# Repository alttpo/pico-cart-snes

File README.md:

# pico-cart-snes
Raspberry Pi Pico SNES flash cart (no SD card, WIP)

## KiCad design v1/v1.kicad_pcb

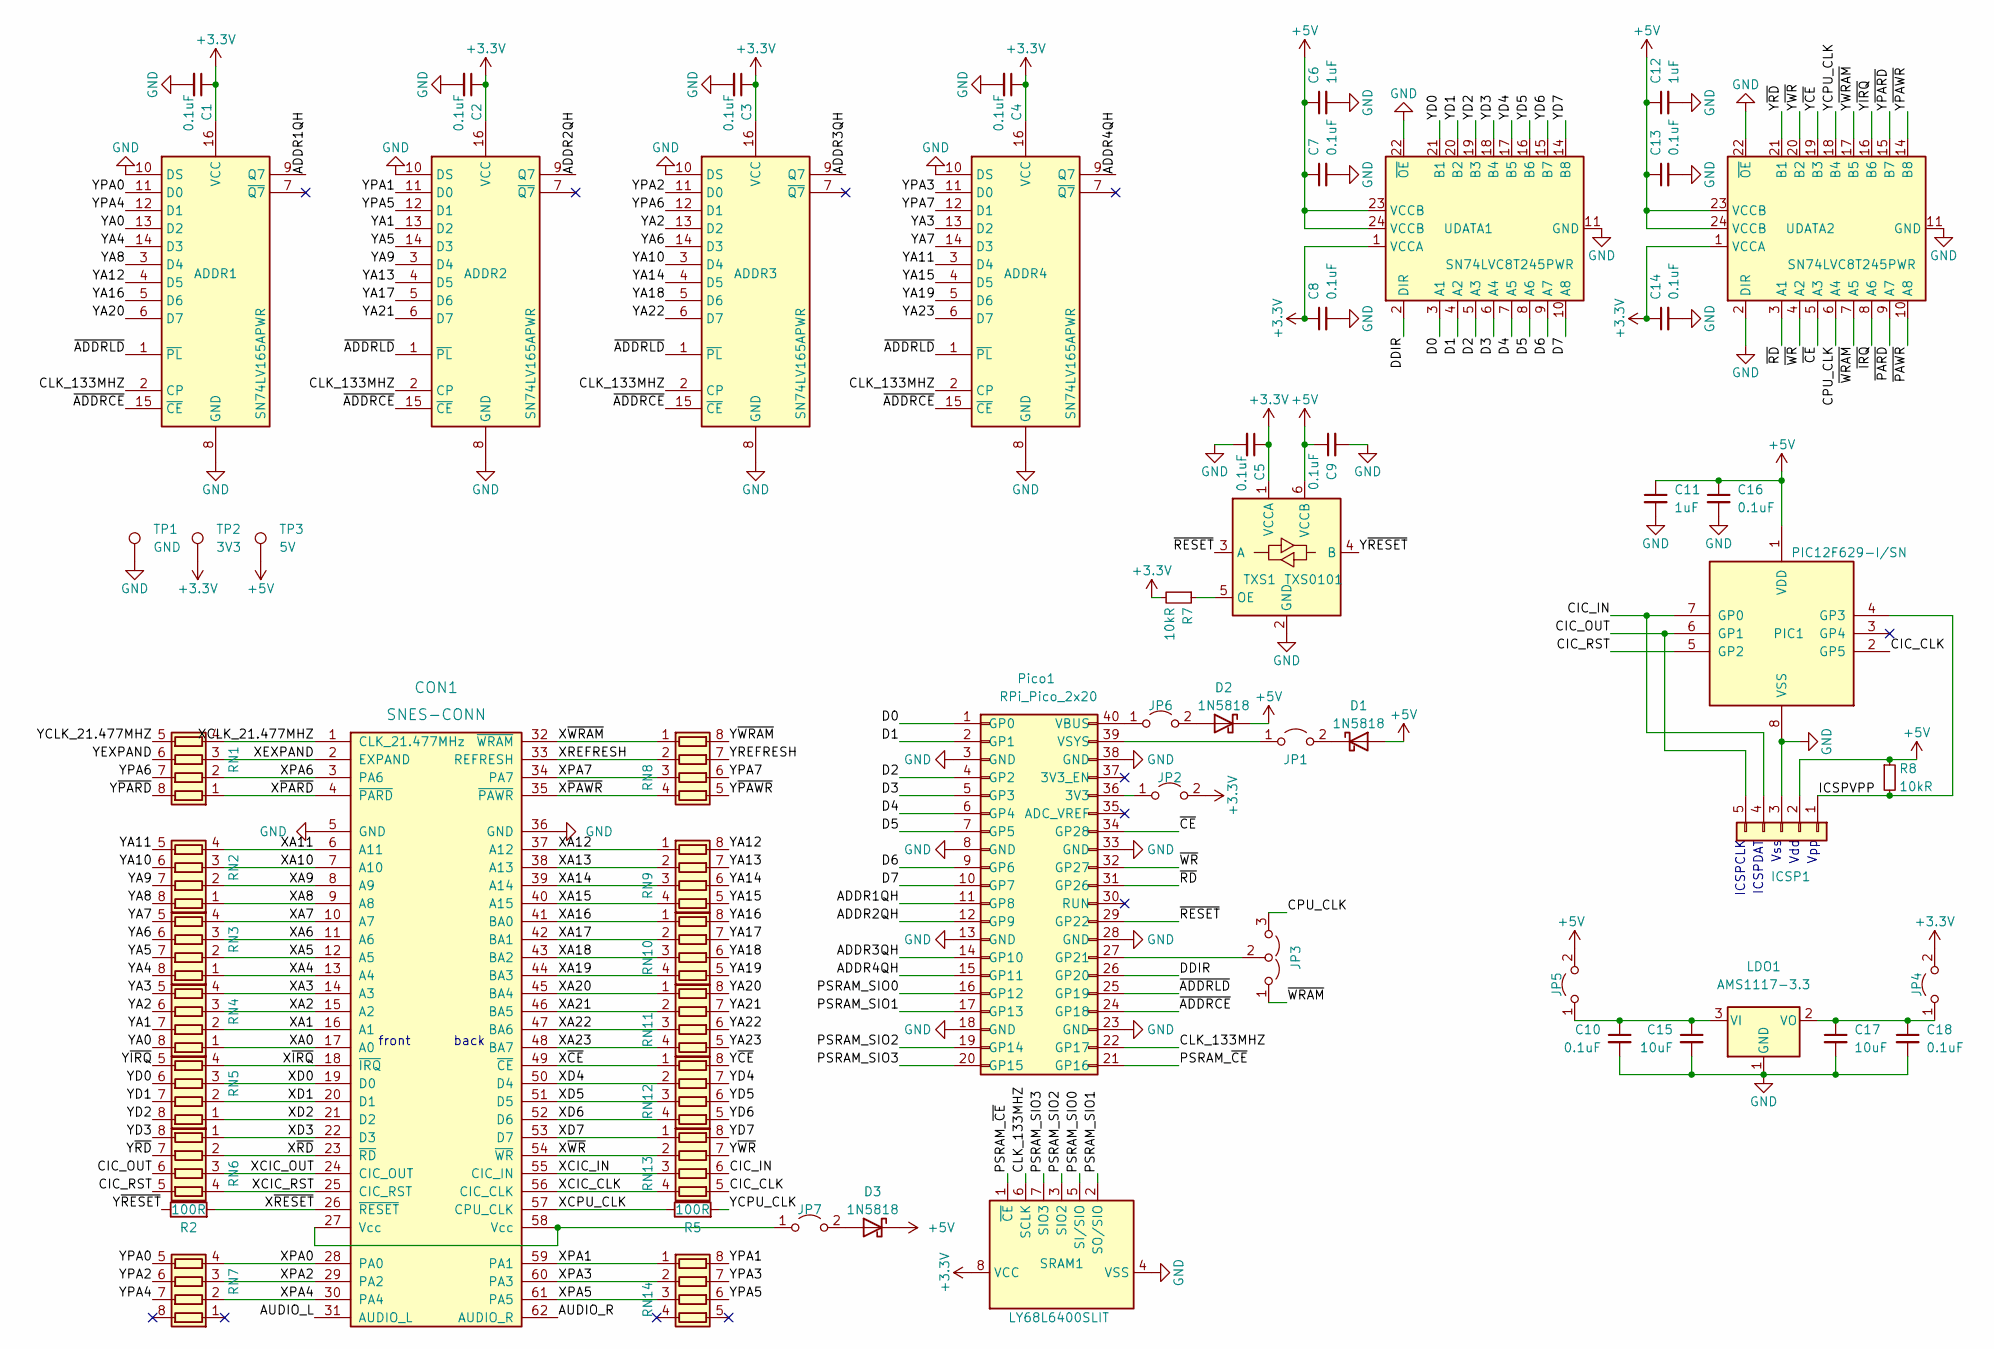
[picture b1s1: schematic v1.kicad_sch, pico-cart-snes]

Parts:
ADDR1, ADDR2, ADDR3, ADDR4: SN74LV165APWR; TSSOP-16_4.4x5mm_P0.65mm; LCSC C201716
C1, C2, C3, C4, C5, C7, C8, C9, C10, C13, C14, C16, C18: 0.1uF; C_1206_3216Metric_Pad1.33x1.80mm_HandSolder; JLC 1206
C6, C11, C12: 1uF; C_1206_3216Metric_Pad1.33x1.80mm_HandSolder; JLC 1206
C15, C17: 10uF; C_1206_3216Metric_Pad1.33x1.80mm_HandSolder; JLC 1206
CON1: SNES-CONN; SNESCART_EXT2
D1, D2, D3: 1N5818; D_SMA_Handsoldering; LCSC C513476
ICSP1: PIC12_ICSP; PinHeader_1x05_P2.54mm_Vertical; LCSC C390683
JP1: PICO_5V_IN; PinHeader_1x02_P2.54mm_Vertical; LCSC C390678
JP2: PICO_3V3_OUT; PinHeader_1x02_P2.54mm_Vertical; LCSC C390678
JP3: WRAM_OR_CLK; PinHeader_1x03_P2.54mm_Vertical; LCSC C390679
JP4: LDO_3V3_OUT; PinHeader_1x02_P2.54mm_Vertical; LCSC C390678
JP5: LDO_5V_IN; PinHeader_1x02_P2.54mm_Vertical; LCSC C390678
JP6: PICO_5V_OUT; PinHeader_1x02_P2.54mm_Vertical; LCSC C390678
JP7: SNES_5V_OUT; PinHeader_1x02_P2.54mm_Vertical; LCSC C390678
LDO1: AMS1117-3.3; SOT-223-3_TabPin2; LCSC C426566
PIC1: PIC12F629-I/SN; SOIC-8_3.9x4.9mm_P1.27mm; LCSC C8226
Pico1: RPi_Pico_2x20; LCSC C429964
R2, R5: 100R; R_1206_3216Metric_Pad1.30x1.75mm_HandSolder; JLC 1206
R7, R8: 10kR; R_1206_3216Metric_Pad1.30x1.75mm_HandSolder; JLC 1206
RN1, RN2, RN3, RN4, RN5, RN6, RN7, RN8, RN9, RN10, RN11, RN12, RN13, RN14: 100R; R_Array_Concave_4x0603; LCSC C79203
SRAM1: LY68L6400SLIT; SOIC-8_3.9x4.9mm_P1.27mm; LCSC C261881
TP1: GND; TestPoint_THTPad_D2.0mm_Drill1.0mm
TP2: 3V3; TestPoint_THTPad_D2.0mm_Drill1.0mm
TP3: 5V; TestPoint_THTPad_D2.0mm_Drill1.0mm
TXS1: TXS0101; SOT-23-6_Handsoldering; LCSC C2677420
UDATA1, UDATA2: SN74LVC8T245PWR; TSSOP-24_4.4x7.8mm_P0.65mm; LCSC C27643

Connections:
+3.3V: ADDR1.16 (VCC), ADDR2.16 (VCC), ADDR3.16 (VCC), ADDR4.16 (VCC), C1.1, C2.1, C3.1, C4.1, C5.1, C8.1, C14.1, JP2.2 (B), JP4.2 (B), R7.2, SRAM1.8 (VCC), TP2.1, TXS1.1 (VCCA), UDATA1.1 (VCCA), UDATA2.1 (VCCA)
+5V: C6.1, C7.1, C9.1, C11.1, C12.1, C13.1, C16.1, D1.2 (A), D2.1 (K), D3.1 (K), ICSP1.2, JP5.2 (B), PIC1.1 (VDD), R8.1, TP3.1, TXS1.6 (VCCB), UDATA1.23 (VCCB), UDATA1.24 (VCCB), UDATA2.23 (VCCB), UDATA2.24 (VCCB)
/ADDR1QH: ADDR1.9 (Q7), Pico1.11 (GP8)
/ADDR2QH: ADDR2.9 (Q7), Pico1.12 (GP9)
/ADDR3QH: ADDR3.9 (Q7), Pico1.14 (GP10)
/ADDR4QH: ADDR4.9 (Q7), Pico1.15 (GP11)
/AUDIO_L: CON1.31 (AUDIO_L)
/AUDIO_R: CON1.62 (AUDIO_R)
/CIC_CLK: PIC1.2 (GP5), RN13.5 (R4.2)
/CIC_IN: ICSP1.4, PIC1.7 (GP0), RN13.6 (R3.2)
/CIC_OUT: ICSP1.5, PIC1.6 (GP1), RN6.6 (R3.2)
/CIC_RST: PIC1.5 (GP2), RN6.5 (R4.2)
/CLK_133MHZ: ADDR1.2 (CP), ADDR2.2 (CP), ADDR3.2 (CP), ADDR4.2 (CP), Pico1.22 (GP17), SRAM1.6 (SCLK)
/CPU_CLK: JP3.3 (B), UDATA2.6 (A4)
/D0: Pico1.1 (GP0), UDATA1.3 (A1)
/D1: Pico1.2 (GP1), UDATA1.4 (A2)
/D2: Pico1.4 (GP2), UDATA1.5 (A3)
/D3: Pico1.5 (GP3), UDATA1.6 (A4)
/D4: Pico1.6 (GP4), UDATA1.7 (A5)
/D5: Pico1.7 (GP5), UDATA1.8 (A6)
/D6: Pico1.9 (GP6), UDATA1.9 (A7)
/D7: Pico1.10 (GP7), UDATA1.10 (A8)
/DDIR: Pico1.26 (GP20), UDATA1.2 (DIR)
/ICSPVPP: ICSP1.1, PIC1.4 (GP3), R8.2
/PSRAM_SIO0: Pico1.16 (GP12), SRAM1.5 (SI/SIO)
/PSRAM_SIO1: Pico1.17 (GP13), SRAM1.2 (SO/SIO)
/PSRAM_SIO2: Pico1.19 (GP14), SRAM1.3 (SIO2)
/PSRAM_SIO3: Pico1.20 (GP15), SRAM1.7 (SIO3)
/PSRAM_~CE: Pico1.21 (GP16), SRAM1.1 (~CE)
/XA0: CON1.17 (A0), RN4.1 (R1.1)
/XA1: CON1.16 (A1), RN4.2 (R2.1)
/XA2: CON1.15 (A2), RN4.3 (R3.1)
/XA3: CON1.14 (A3), RN4.4 (R4.1)
/XA4: CON1.13 (A4), RN3.1 (R1.1)
/XA5: CON1.12 (A5), RN3.2 (R2.1)
/XA6: CON1.11 (A6), RN3.3 (R3.1)
/XA7: CON1.10 (A7), RN3.4 (R4.1)
/XA8: CON1.9 (A8), RN2.1 (R1.1)
/XA9: CON1.8 (A9), RN2.2 (R2.1)
/XA10: CON1.7 (A10), RN2.3 (R3.1)
/XA11: CON1.6 (A11), RN2.4 (R4.1)
/XA12: CON1.37 (A12), RN9.1 (R1.1)
/XA13: CON1.38 (A13), RN9.2 (R2.1)
/XA14: CON1.39 (A14), RN9.3 (R3.1)
/XA15: CON1.40 (A15), RN9.4 (R4.1)
/XA16: CON1.41 (BA0), RN10.1 (R1.1)
/XA17: CON1.42 (BA1), RN10.2 (R2.1)
/XA18: CON1.43 (BA2), RN10.3 (R3.1)
/XA19: CON1.44 (BA3), RN10.4 (R4.1)
/XA20: CON1.45 (BA4), RN11.1 (R1.1)
/XA21: CON1.46 (BA5), RN11.2 (R2.1)
/XA22: CON1.47 (BA6), RN11.3 (R3.1)
/XA23: CON1.48 (BA7), RN11.4 (R4.1)
/XCIC_CLK: CON1.56 (CIC_CLK), RN13.4 (R4.1)
/XCIC_IN: CON1.55 (CIC_IN), RN13.3 (R3.1)
/XCIC_OUT: CON1.24 (CIC_OUT), RN6.3 (R3.1)
/XCIC_RST: CON1.25 (CIC_RST), RN6.4 (R4.1)
/XCLK_21.477MHZ: CON1.1 (CLK_21.477MHz), RN1.4 (R4.1)
/XCPU_CLK: CON1.57 (CPU_CLK), R5.1
/XD0: CON1.19 (D0), RN5.3 (R3.1)
/XD1: CON1.20 (D1), RN5.2 (R2.1)
/XD2: CON1.21 (D2), RN5.1 (R1.1)
/XD3: CON1.22 (D3), RN6.1 (R1.1)
/XD4: CON1.50 (D4), RN12.2 (R2.1)
/XD5: CON1.51 (D5), RN12.3 (R3.1)
/XD6: CON1.52 (D6), RN12.4 (R4.1)
/XD7: CON1.53 (D7), RN13.1 (R1.1)
/XEXPAND: CON1.2 (EXPAND), RN1.3 (R3.1)
/XPA0: CON1.28 (PA0), RN7.4 (R4.1)
/XPA1: CON1.59 (PA1), RN14.1 (R1.1)
/XPA2: CON1.29 (PA2), RN7.3 (R3.1)
/XPA3: CON1.60 (PA3), RN14.2 (R2.1)
/XPA4: CON1.30 (PA4), RN7.2 (R2.1)
/XPA5: CON1.61 (PA5), RN14.3 (R3.1)
/XPA6: CON1.3 (PA6), RN1.2 (R2.1)
/XPA7: CON1.34 (PA7), RN8.3 (R3.1)
/XREFRESH: CON1.33 (REFRESH), RN8.2 (R2.1)
/X~CE: CON1.49 (~CE), RN12.1 (R1.1)
/X~IRQ: CON1.18 (~IRQ), RN5.4 (R4.1)
/X~PARD: CON1.4 (~PARD), RN1.1 (R1.1)
/X~PAWR: CON1.35 (~PAWR), RN8.4 (R4.1)
/X~RD: CON1.23 (~RD), RN6.2 (R2.1)
/X~RESET: CON1.26 (~RESET), R2.2
/X~WRAM: CON1.32 (~WRAM), RN8.1 (R1.1)
/X~WR: CON1.54 (~WR), RN13.2 (R2.1)
/YA0: ADDR1.13 (D2), RN4.8 (R1.2)
/YA1: ADDR2.13 (D2), RN4.7 (R2.2)
/YA2: ADDR3.13 (D2), RN4.6 (R3.2)
/YA3: ADDR4.13 (D2), RN4.5 (R4.2)
/YA4: ADDR1.14 (D3), RN3.8 (R1.2)
/YA5: ADDR2.14 (D3), RN3.7 (R2.2)
/YA6: ADDR3.14 (D3), RN3.6 (R3.2)
/YA7: ADDR4.14 (D3), RN3.5 (R4.2)
/YA8: ADDR1.3 (D4), RN2.8 (R1.2)
/YA9: ADDR2.3 (D4), RN2.7 (R2.2)
/YA10: ADDR3.3 (D4), RN2.6 (R3.2)
/YA11: ADDR4.3 (D4), RN2.5 (R4.2)
/YA12: ADDR1.4 (D5), RN9.8 (R1.2)
/YA13: ADDR2.4 (D5), RN9.7 (R2.2)
/YA14: ADDR3.4 (D5), RN9.6 (R3.2)
/YA15: ADDR4.4 (D5), RN9.5 (R4.2)
/YA16: ADDR1.5 (D6), RN10.8 (R1.2)
/YA17: ADDR2.5 (D6), RN10.7 (R2.2)
/YA18: ADDR3.5 (D6), RN10.6 (R3.2)
/YA19: ADDR4.5 (D6), RN10.5 (R4.2)
/YA20: ADDR1.6 (D7), RN11.8 (R1.2)
/YA21: ADDR2.6 (D7), RN11.7 (R2.2)
/YA22: ADDR3.6 (D7), RN11.6 (R3.2)
/YA23: ADDR4.6 (D7), RN11.5 (R4.2)
/YCLK_21.477MHZ: RN1.5 (R4.2)
/YCPU_CLK: R5.2, UDATA2.18 (B4)
/YD0: RN5.6 (R3.2), UDATA1.21 (B1)
/YD1: RN5.7 (R2.2), UDATA1.20 (B2)
/YD2: RN5.8 (R1.2), UDATA1.19 (B3)
/YD3: RN6.8 (R1.2), UDATA1.18 (B4)
/YD4: RN12.7 (R2.2), UDATA1.17 (B5)
/YD5: RN12.6 (R3.2), UDATA1.16 (B6)
/YD6: RN12.5 (R4.2), UDATA1.15 (B7)
/YD7: RN13.8 (R1.2), UDATA1.14 (B8)
/YEXPAND: RN1.6 (R3.2)
/YPA0: ADDR1.11 (D0), RN7.5 (R4.2)
/YPA1: ADDR2.11 (D0), RN14.8 (R1.2)
/YPA2: ADDR3.11 (D0), RN7.6 (R3.2)
/YPA3: ADDR4.11 (D0), RN14.7 (R2.2)
/YPA4: ADDR1.12 (D1), RN7.7 (R2.2)
/YPA5: ADDR2.12 (D1), RN14.6 (R3.2)
/YPA6: ADDR3.12 (D1), RN1.7 (R2.2)
/YPA7: ADDR4.12 (D1), RN8.6 (R3.2)
/YREFRESH: RN8.7 (R2.2)
/Y~CE: RN12.8 (R1.2), UDATA2.19 (B3)
/Y~IRQ: RN5.5 (R4.2), UDATA2.16 (B6)
/Y~PARD: RN1.8 (R1.2), UDATA2.15 (B7)
/Y~PAWR: RN8.5 (R4.2), UDATA2.14 (B8)
/Y~RD: RN6.7 (R2.2), UDATA2.21 (B1)
/Y~RESET: R2.1, TXS1.4 (B)
/Y~WRAM: RN8.8 (R1.2), UDATA2.17 (B5)
/Y~WR: RN13.7 (R2.2), UDATA2.20 (B2)
/~ADDRCE: ADDR1.15 (~CE), ADDR2.15 (~CE), ADDR3.15 (~CE), ADDR4.15 (~CE), Pico1.24 (GP18)
/~ADDRLD: ADDR1.1 (~PL), ADDR2.1 (~PL), ADDR3.1 (~PL), ADDR4.1 (~PL), Pico1.25 (GP19)
/~CE: Pico1.34 (GP28), UDATA2.5 (A3)
/~IRQ: UDATA2.8 (A6)
/~PARD: UDATA2.9 (A7)
/~PAWR: UDATA2.10 (A8)
/~RD: Pico1.31 (GP26), UDATA2.3 (A1)
/~RESET: Pico1.29 (GP22), TXS1.3 (A)
/~WRAM: JP3.1 (A), UDATA2.7 (A5)
/~WR: Pico1.32 (GP27), UDATA2.4 (A2)
GND: ADDR1.8 (GND), ADDR1.10 (DS), ADDR2.8 (GND), ADDR2.10 (DS), ADDR3.8 (GND), ADDR3.10 (DS), ADDR4.8 (GND), ADDR4.10 (DS), C1.2, C2.2, C3.2, C4.2, C5.2, C6.2, C7.2, C8.2, C9.2, C10.2, C11.2, C12.2, C13.2, C14.2, C15.2, C16.2, C17.2, C18.2, CON1.5 (GND), CON1.36 (GND), ICSP1.3, LDO1.1 (GND), PIC1.8 (VSS), Pico1.3 (GND), Pico1.8 (GND), Pico1.13 (GND), Pico1.18 (GND), Pico1.23 (GND), Pico1.28 (GND), Pico1.33 (GND), Pico1.38 (GND), SRAM1.4 (VSS), TP1.1, TXS1.2 (GND), UDATA1.11 (GND), UDATA1.12 (GND), UDATA1.13 (GND), UDATA1.22 (~OE), UDATA2.2 (DIR), UDATA2.11 (GND), UDATA2.12 (GND), UDATA2.13 (GND), UDATA2.22 (~OE)
unnamed: C10.1, C15.1, JP5.1 (A), LDO1.3 (VI)
unnamed: C17.1, C18.1, JP4.1 (A), LDO1.2 (VO)
unnamed: CON1.27 (Vcc), CON1.58 (Vcc), JP7.1 (A)
unnamed: D1.1 (K), JP1.2 (B)
unnamed: D2.2 (A), JP6.2 (B)
unnamed: D3.2 (A), JP7.2 (B)
unnamed: JP1.1 (A), Pico1.39 (VSYS)
unnamed: JP2.1 (A), Pico1.36 (3V3)
unnamed: JP3.2 (C), Pico1.27 (GP21)
unnamed: JP6.1 (A), Pico1.40 (VBUS)
unnamed: R7.1, TXS1.5 (OE)

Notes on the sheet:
Vpp
Vss
ICSPCLK
Vdd
front
ICSPDAT
back

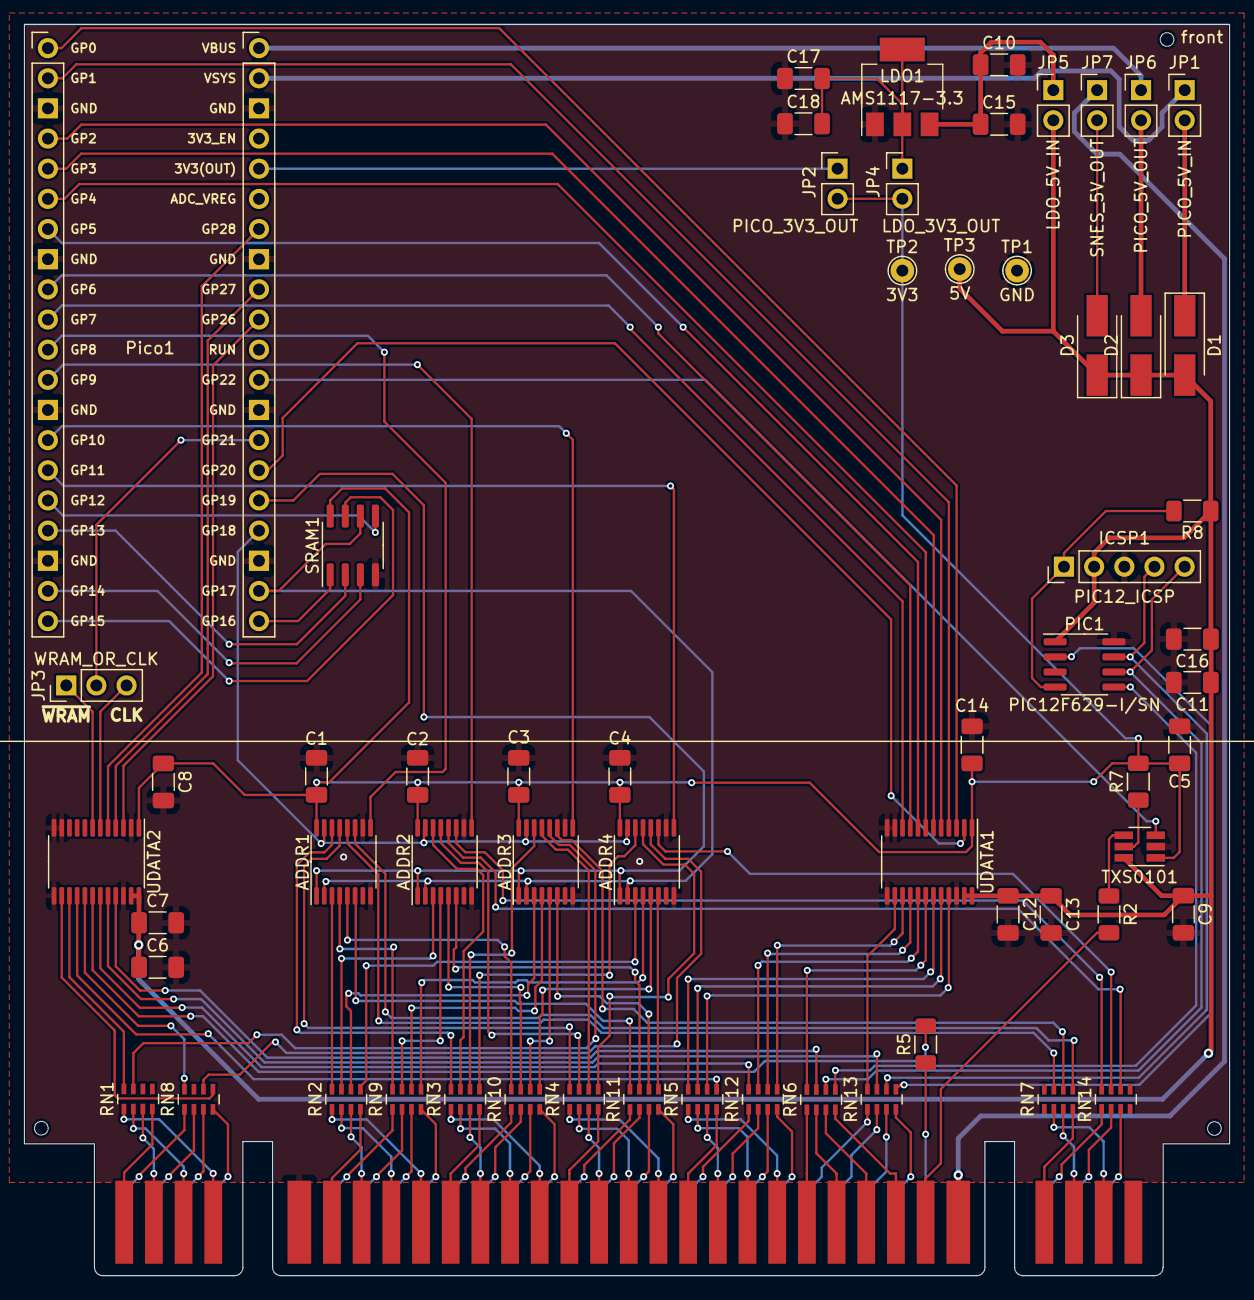
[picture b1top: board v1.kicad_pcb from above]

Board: 2 copper layers, 101.5 x 105.4 mm, 62 parts (0 on the bottom side), 151 nets.

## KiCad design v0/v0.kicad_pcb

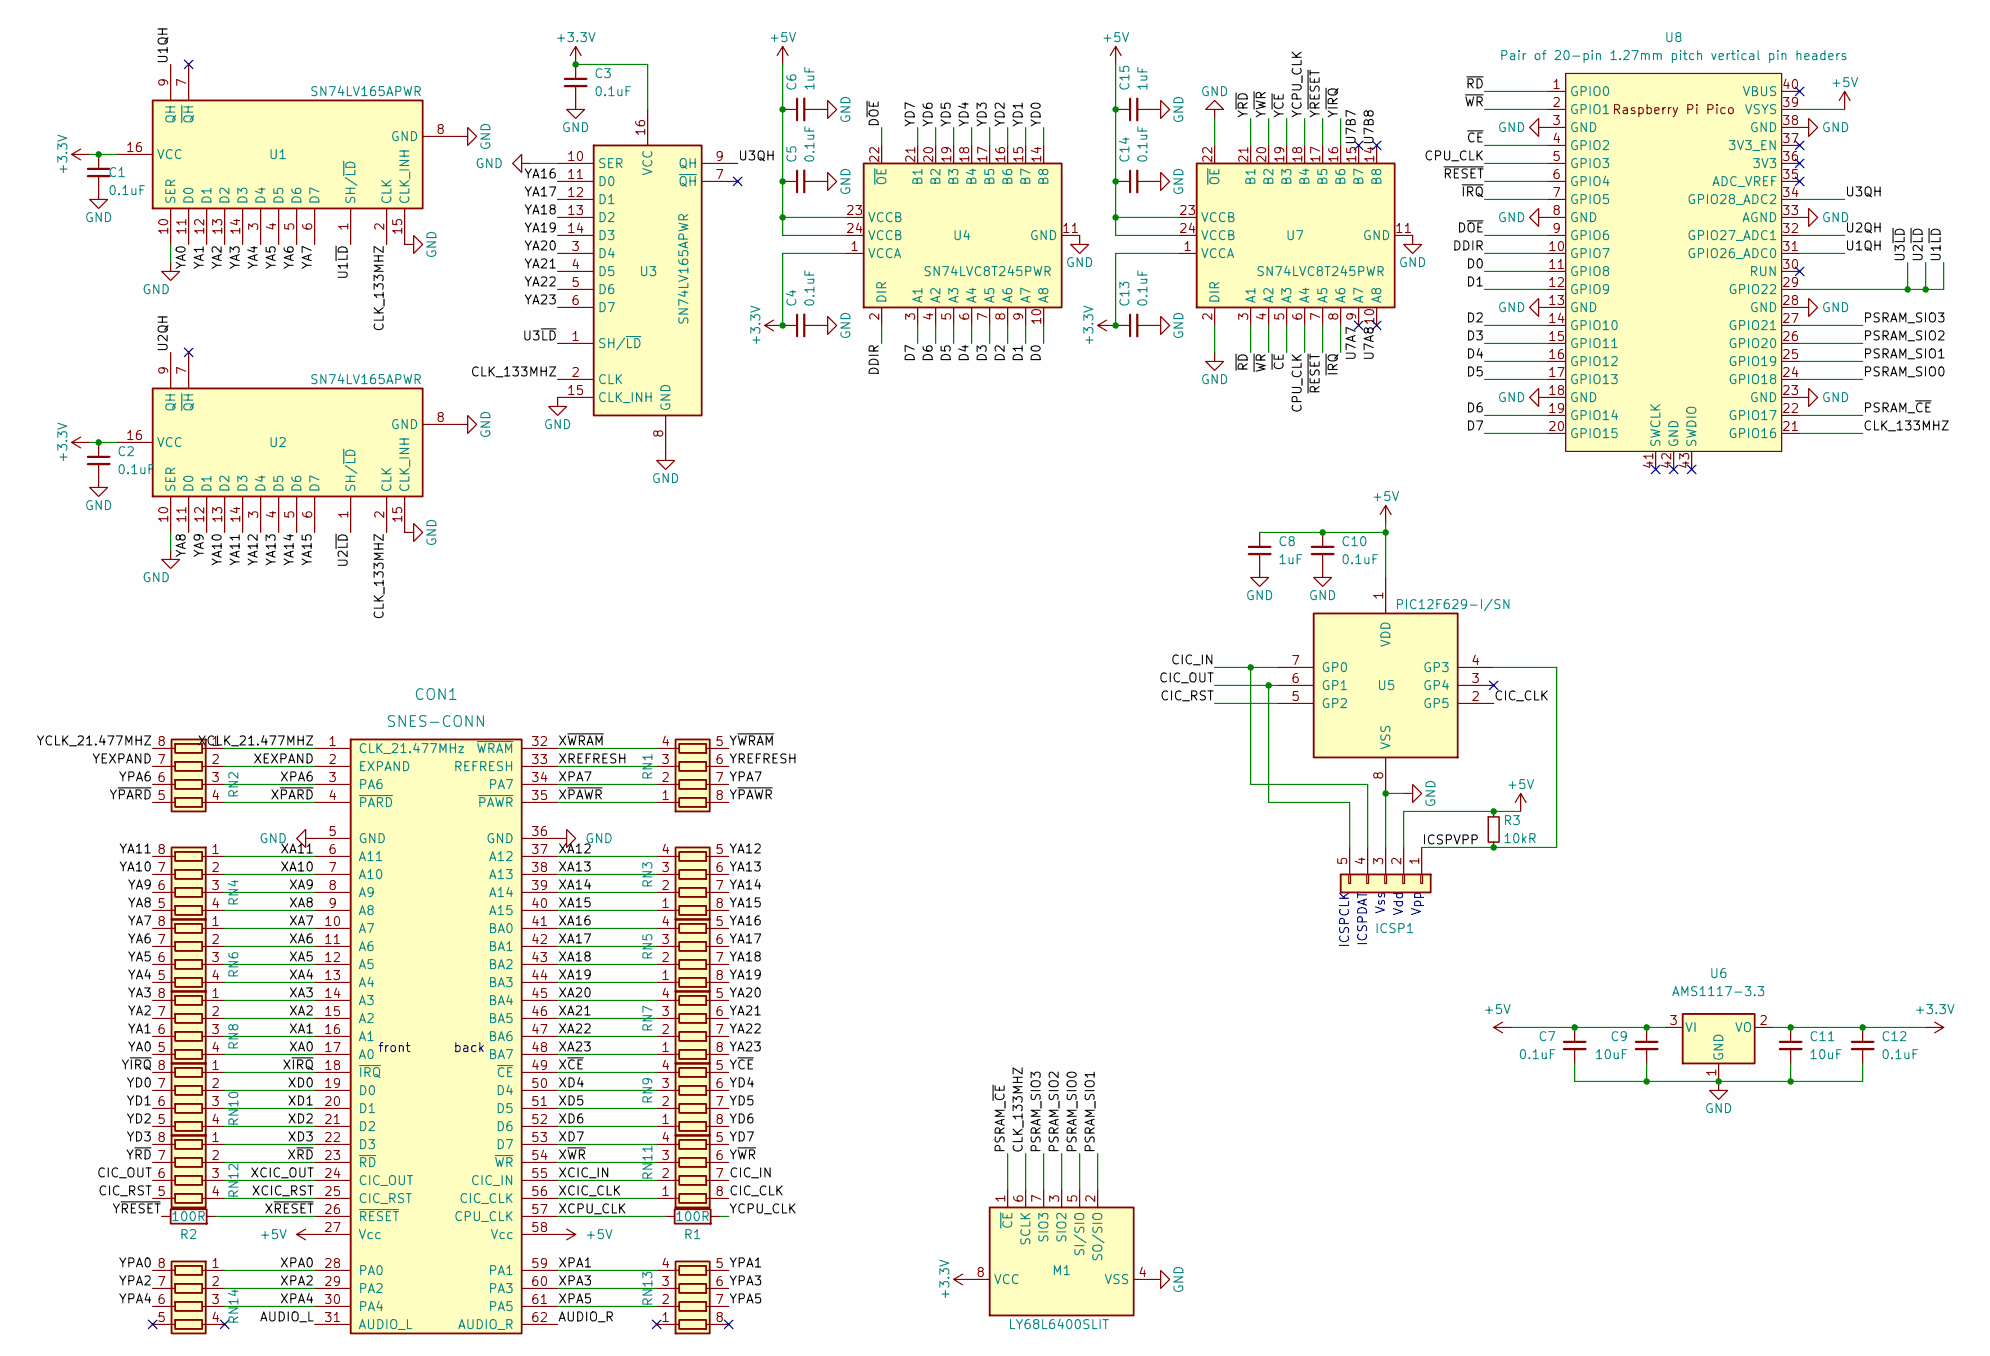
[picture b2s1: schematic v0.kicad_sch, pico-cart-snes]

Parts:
C1, C2, C3, C4, C5, C7, C10, C12, C13, C14: 0.1uF; C_1206_3216Metric_Pad1.33x1.80mm_HandSolder; JLC 1206
C6, C8, C15: 1uF; C_1206_3216Metric_Pad1.33x1.80mm_HandSolder; JLC 1206
C9, C11: 10uF; C_1206_3216Metric_Pad1.33x1.80mm_HandSolder; JLC 1206
CON1: SNES-CONN; SNESCART_EXT2_SMTUSB
ICSP1: Conn_01x05; PinHeader_1x05_P2.54mm_Vertical; LCSC C492404
M1: LY68L6400SLIT; SOIC-8_3.9x4.9mm_P1.27mm; LCSC LY68L6400SLIT
R1, R2: 100R; R_1206_3216Metric_Pad1.30x1.75mm_HandSolder; JLC 1206_R
R3: 10kR; R_1206_3216Metric_Pad1.30x1.75mm_HandSolder; JLC 1206_R
RN1, RN2, RN3, RN4, RN5, RN6, RN7, RN8, RN9, RN10, RN11, RN12, RN13, RN14: 100R; R_Array_Concave_4x0603; LCSC C79203
U1, U2, U3: SN74LV165APWR; TSSOP-16_4.4x5mm_P0.65mm; LCSC C201716
U4, U7: SN74LVC8T245PWR; TSSOP-24_4.4x7.8mm_P0.65mm; LCSC C27643
U5: PIC12F629-I/SN; SOIC-8_3.9x4.9mm_P1.27mm; LCSC C8226
U6: AMS1117-3.3; SOT-223-3_TabPin2; LCSC C426566
U8: Pair of 20-pin 1.27mm pitch vertical pin headers; RPi_Pico_SMD_TH

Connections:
+3.3V: C1.1, C2.1, C3.1, C4.1, C11.1, C12.1, C13.1, M1.8 (VCC), U1.16 (VCC), U2.16 (VCC), U3.16 (VCC), U4.1 (VCCA), U6.2 (VO), U7.1 (VCCA)
+5V: C5.1, C6.1, C7.1, C8.1, C9.1, C10.1, C14.1, C15.1, CON1.27 (Vcc), CON1.58 (Vcc), ICSP1.2, R3.1, U4.23 (VCCB), U4.24 (VCCB), U5.1 (VDD), U6.3 (VI), U7.23 (VCCB), U7.24 (VCCB), U8.39 (VSYS)
/AUDIO_L: CON1.31 (AUDIO_L)
/AUDIO_R: CON1.62 (AUDIO_R)
/CIC_CLK: RN11.8 (R1.2), U5.2 (GP5)
/CIC_IN: ICSP1.4, RN11.7 (R2.2), U5.7 (GP0)
/CIC_OUT: ICSP1.5, RN12.6 (R3.2), U5.6 (GP1)
/CIC_RST: RN12.5 (R4.2), U5.5 (GP2)
/CLK_133MHZ: M1.6 (SCLK), U1.2 (CLK), U2.2 (CLK), U3.2 (CLK), U8.21 (GPIO16)
/CPU_CLK: U7.6 (A4), U8.5 (GPIO3)
/D0: U4.10 (A8), U8.11 (GPIO8)
/D1: U4.9 (A7), U8.12 (GPIO9)
/D2: U4.8 (A6), U8.14 (GPIO10)
/D3: U4.7 (A5), U8.15 (GPIO11)
/D4: U4.6 (A4), U8.16 (GPIO12)
/D5: U4.5 (A3), U8.17 (GPIO13)
/D6: U4.4 (A2), U8.19 (GPIO14)
/D7: U4.3 (A1), U8.20 (GPIO15)
/DDIR: U4.2 (DIR), U8.10 (GPIO7)
/D~OE: U4.22 (~OE), U8.9 (GPIO6)
/ICSPVPP: ICSP1.1, R3.2, U5.4 (GP3)
/PSRAM_SIO0: M1.5 (SI/SIO), U8.24 (GPIO18)
/PSRAM_SIO1: M1.2 (SO/SIO), U8.25 (GPIO19)
/PSRAM_SIO2: M1.3 (SIO2), U8.26 (GPIO20)
/PSRAM_SIO3: M1.7 (SIO3), U8.27 (GPIO21)
/PSRAM_~CE: M1.1 (~CE), U8.22 (GPIO17)
/U1QH: U1.9 (QH), U8.31 (GPIO26_ADC0)
/U1~LD: U1.1 (SH/~LD), U2.1 (SH/~LD), U3.1 (SH/~LD), U8.29 (GPIO22)
/U2QH: U2.9 (QH), U8.32 (GPIO27_ADC1)
/U3QH: U3.9 (QH), U8.34 (GPIO28_ADC2)
/U7A7: U7.9 (A7)
/U7A8: U7.10 (A8)
/U7B7: U7.15 (B7)
/U7B8: U7.14 (B8)
/XA0: CON1.17 (A0), RN8.4 (R4.1)
/XA1: CON1.16 (A1), RN8.3 (R3.1)
/XA2: CON1.15 (A2), RN8.2 (R2.1)
/XA3: CON1.14 (A3), RN8.1 (R1.1)
/XA4: CON1.13 (A4), RN6.4 (R4.1)
/XA5: CON1.12 (A5), RN6.3 (R3.1)
/XA6: CON1.11 (A6), RN6.2 (R2.1)
/XA7: CON1.10 (A7), RN6.1 (R1.1)
/XA8: CON1.9 (A8), RN4.4 (R4.1)
/XA9: CON1.8 (A9), RN4.3 (R3.1)
/XA10: CON1.7 (A10), RN4.2 (R2.1)
/XA11: CON1.6 (A11), RN4.1 (R1.1)
/XA12: CON1.37 (A12), RN3.4 (R4.1)
/XA13: CON1.38 (A13), RN3.3 (R3.1)
/XA14: CON1.39 (A14), RN3.2 (R2.1)
/XA15: CON1.40 (A15), RN3.1 (R1.1)
/XA16: CON1.41 (BA0), RN5.4 (R4.1)
/XA17: CON1.42 (BA1), RN5.3 (R3.1)
/XA18: CON1.43 (BA2), RN5.2 (R2.1)
/XA19: CON1.44 (BA3), RN5.1 (R1.1)
/XA20: CON1.45 (BA4), RN7.4 (R4.1)
/XA21: CON1.46 (BA5), RN7.3 (R3.1)
/XA22: CON1.47 (BA6), RN7.2 (R2.1)
/XA23: CON1.48 (BA7), RN7.1 (R1.1)
/XCIC_CLK: CON1.56 (CIC_CLK), RN11.1 (R1.1)
/XCIC_IN: CON1.55 (CIC_IN), RN11.2 (R2.1)
/XCIC_OUT: CON1.24 (CIC_OUT), RN12.3 (R3.1)
/XCIC_RST: CON1.25 (CIC_RST), RN12.4 (R4.1)
/XCLK_21.477MHZ: CON1.1 (CLK_21.477MHz), RN2.1 (R1.1)
/XCPU_CLK: CON1.57 (CPU_CLK), R1.1
/XD0: CON1.19 (D0), RN10.2 (R2.1)
/XD1: CON1.20 (D1), RN10.3 (R3.1)
/XD2: CON1.21 (D2), RN10.4 (R4.1)
/XD3: CON1.22 (D3), RN12.1 (R1.1)
/XD4: CON1.50 (D4), RN9.3 (R3.1)
/XD5: CON1.51 (D5), RN9.2 (R2.1)
/XD6: CON1.52 (D6), RN9.1 (R1.1)
/XD7: CON1.53 (D7), RN11.4 (R4.1)
/XEXPAND: CON1.2 (EXPAND), RN2.2 (R2.1)
/XPA0: CON1.28 (PA0), RN14.1 (R1.1)
/XPA1: CON1.59 (PA1), RN13.4 (R4.1)
/XPA2: CON1.29 (PA2), RN14.2 (R2.1)
/XPA3: CON1.60 (PA3), RN13.3 (R3.1)
/XPA4: CON1.30 (PA4), RN14.3 (R3.1)
/XPA5: CON1.61 (PA5), RN13.2 (R2.1)
/XPA6: CON1.3 (PA6), RN2.3 (R3.1)
/XPA7: CON1.34 (PA7), RN1.2 (R2.1)
/XREFRESH: CON1.33 (REFRESH), RN1.3 (R3.1)
/X~CE: CON1.49 (~CE), RN9.4 (R4.1)
/X~IRQ: CON1.18 (~IRQ), RN10.1 (R1.1)
/X~PARD: CON1.4 (~PARD), RN2.4 (R4.1)
/X~PAWR: CON1.35 (~PAWR), RN1.1 (R1.1)
/X~RD: CON1.23 (~RD), RN12.2 (R2.1)
/X~RESET: CON1.26 (~RESET), R2.2
/X~WRAM: CON1.32 (~WRAM), RN1.4 (R4.1)
/X~WR: CON1.54 (~WR), RN11.3 (R3.1)
/YA0: RN8.5 (R4.2), U1.11 (D0)
/YA1: RN8.6 (R3.2), U1.12 (D1)
/YA2: RN8.7 (R2.2), U1.13 (D2)
/YA3: RN8.8 (R1.2), U1.14 (D3)
/YA4: RN6.5 (R4.2), U1.3 (D4)
/YA5: RN6.6 (R3.2), U1.4 (D5)
/YA6: RN6.7 (R2.2), U1.5 (D6)
/YA7: RN6.8 (R1.2), U1.6 (D7)
/YA8: RN4.5 (R4.2), U2.11 (D0)
/YA9: RN4.6 (R3.2), U2.12 (D1)
/YA10: RN4.7 (R2.2), U2.13 (D2)
/YA11: RN4.8 (R1.2), U2.14 (D3)
/YA12: RN3.5 (R4.2), U2.3 (D4)
/YA13: RN3.6 (R3.2), U2.4 (D5)
/YA14: RN3.7 (R2.2), U2.5 (D6)
/YA15: RN3.8 (R1.2), U2.6 (D7)
/YA16: RN5.5 (R4.2), U3.11 (D0)
/YA17: RN5.6 (R3.2), U3.12 (D1)
/YA18: RN5.7 (R2.2), U3.13 (D2)
/YA19: RN5.8 (R1.2), U3.14 (D3)
/YA20: RN7.5 (R4.2), U3.3 (D4)
/YA21: RN7.6 (R3.2), U3.4 (D5)
/YA22: RN7.7 (R2.2), U3.5 (D6)
/YA23: RN7.8 (R1.2), U3.6 (D7)
/YCLK_21.477MHZ: RN2.8 (R1.2)
/YCPU_CLK: R1.2, U7.18 (B4)
/YD0: RN10.7 (R2.2), U4.14 (B8)
/YD1: RN10.6 (R3.2), U4.15 (B7)
/YD2: RN10.5 (R4.2), U4.16 (B6)
/YD3: RN12.8 (R1.2), U4.17 (B5)
/YD4: RN9.6 (R3.2), U4.18 (B4)
/YD5: RN9.7 (R2.2), U4.19 (B3)
/YD6: RN9.8 (R1.2), U4.20 (B2)
/YD7: RN11.5 (R4.2), U4.21 (B1)
/YEXPAND: RN2.7 (R2.2)
/YPA0: RN14.8 (R1.2)
/YPA1: RN13.5 (R4.2)
/YPA2: RN14.7 (R2.2)
/YPA3: RN13.6 (R3.2)
/YPA4: RN14.6 (R3.2)
/YPA5: RN13.7 (R2.2)
/YPA6: RN2.6 (R3.2)
/YPA7: RN1.7 (R2.2)
/YREFRESH: RN1.6 (R3.2)
/Y~CE: RN9.5 (R4.2), U7.19 (B3)
/Y~IRQ: RN10.8 (R1.2), U7.16 (B6)
/Y~PARD: RN2.5 (R4.2)
/Y~PAWR: RN1.8 (R1.2)
/Y~RD: RN12.7 (R2.2), U7.21 (B1)
/Y~RESET: R2.1, U7.17 (B5)
/Y~WRAM: RN1.5 (R4.2)
/Y~WR: RN11.6 (R3.2), U7.20 (B2)
/~CE: U7.5 (A3), U8.4 (GPIO2)
/~IRQ: U7.8 (A6), U8.7 (GPIO5)
/~RD: U7.3 (A1), U8.1 (GPIO0)
/~RESET: U7.7 (A5), U8.6 (GPIO4)
/~WR: U7.4 (A2), U8.2 (GPIO1)
GND: C1.2, C2.2, C3.2, C4.2, C5.2, C6.2, C7.2, C8.2, C9.2, C10.2, C11.2, C12.2, C13.2, C14.2, C15.2, CON1.5 (GND), CON1.36 (GND), ICSP1.3, M1.4 (VSS), U1.8 (GND), U1.10 (SER), U1.15 (CLK_INH), U2.8 (GND), U2.10 (SER), U2.15 (CLK_INH), U3.8 (GND), U3.10 (SER), U3.15 (CLK_INH), U4.11 (GND), U4.12 (GND), U4.13 (GND), U5.8 (VSS), U6.1 (GND), U7.2 (DIR), U7.11 (GND), U7.12 (GND), U7.13 (GND), U7.22 (~OE), U8.3 (GND), U8.8 (GND), U8.13 (GND), U8.18 (GND), U8.23 (GND), U8.28 (GND), U8.33 (AGND), U8.38 (GND)

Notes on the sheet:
Vpp
Vss
ICSPCLK
Vdd
front
ICSPDAT
back

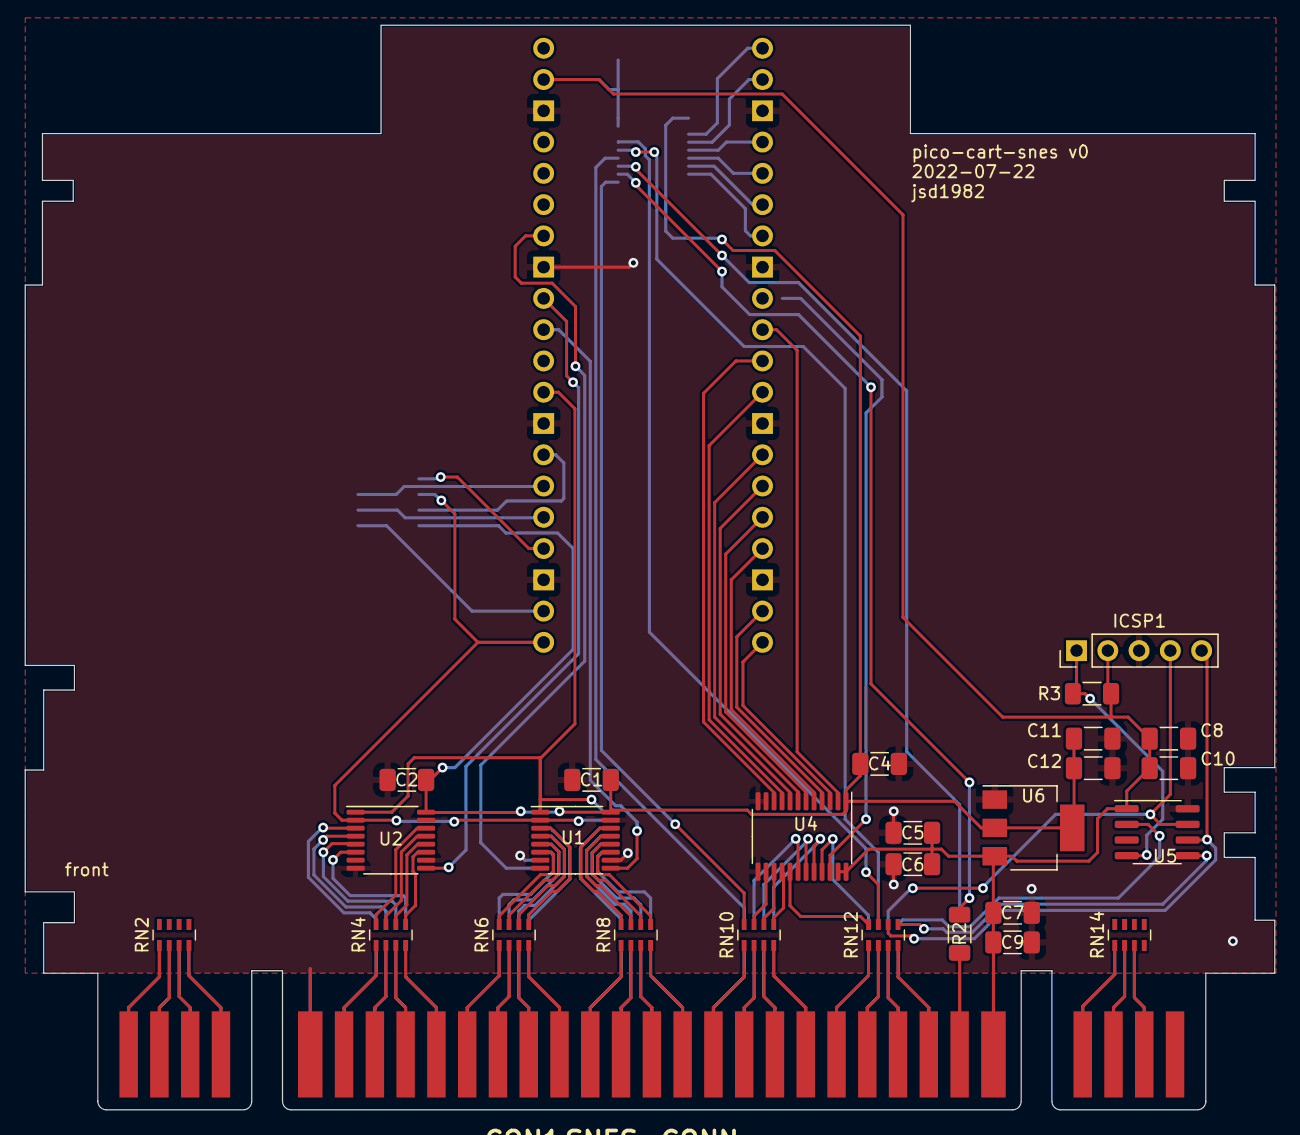
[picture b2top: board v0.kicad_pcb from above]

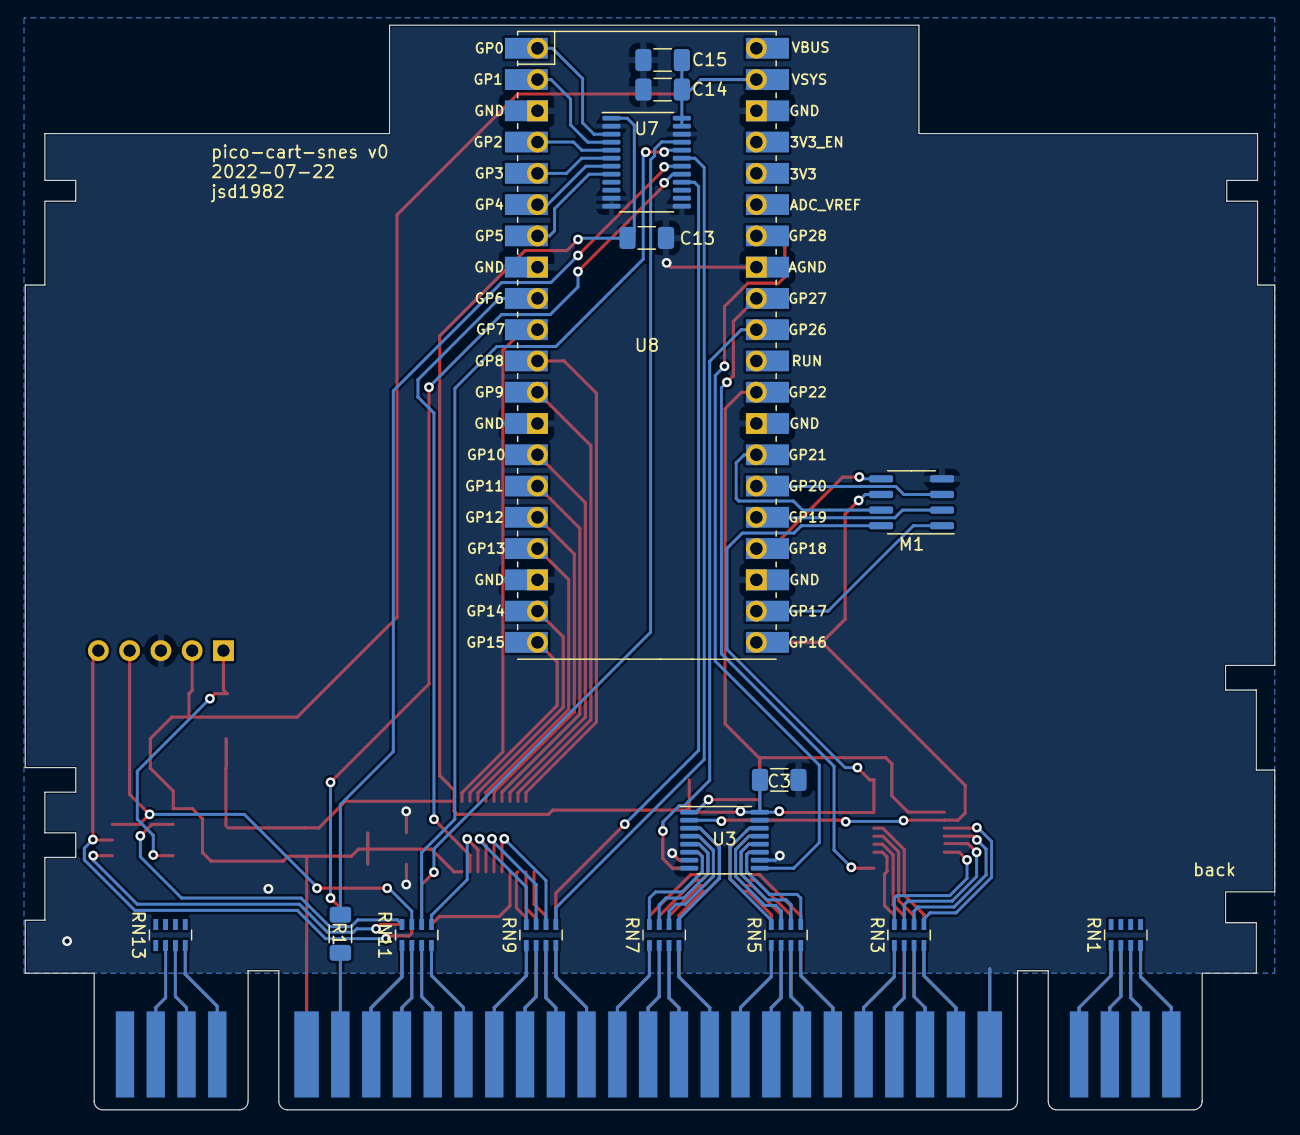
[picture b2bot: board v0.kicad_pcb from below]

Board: 2 copper layers, 101.5 x 88.1 mm, 43 parts (16 on the bottom side), 128 nets.

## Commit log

2022-07-21 Initial commit of v0 of pico-cart-snes project including SNES connector and labeled pins
2022-07-21 Routed shift registers
2022-07-21 Route through 100R networks and into shift registers for address lines
2022-07-21 Added PIC12F and 3.3V supply; routed all nets
2022-07-22 Added RPi Pico footprint and routed traces to it
2022-07-22 Connect /OE to GND; fix up minor routing
2022-07-22 Added front and back indicators; added title
2022-07-22 Add title to back layer; render front/back PCB and schematic
2022-07-23 Critical fix to PSRAM to control /CE pin from Pico; add LCSC properties to all parts; add ICSP header for PIC12F
2022-07-23 Add JLC properties; re-render front,back,pdf
2022-07-23 Fix resistor array footprints and reroute; new layout of GPIO pins for PSRAM vs SNES address to be contiguous pin numbers
2022-07-24 Add LCSC and MOUSER part numbers
2022-07-24 Generated gerber files
2022-07-30 Made v1 copy of v0 with new routing for diode and jumper for VSYS of Pico
2022-07-30 v1: replace Pico component with pair of pin headers
2022-08-06 v1: redo shift regs; redo gpio pin assignments; add jumpers for LDO vs Pico 3V3 power supply; use TXS0101 for /RESET
2022-08-07 v1: fixed /WRAM vs CPU_CLK jumper selector to make sense; lots of PCB routing decisions
2022-08-09 v1: lots of routing and better placement of components
2022-08-09 v1: cleaned up more routing
2022-08-09 v1: more routing progress
2022-08-10 v1: completed routing
2022-08-10 v1: added jumper and diode for SNES 5V supply feeding +5V rail
2022-08-10 v1: increase 5V traces to 0.5mm; add renders
2022-08-10 v1: updated footprint of RPi Pico to include pin labels; added test points for power rails
2022-08-10 v1: added LCSC part numbers; switched out diodes for SMT; 74LV166A is out of stock at LCSC so need to replace it
2022-08-11 v1: restarting routing of shift registers in new orientation with replacement components
2022-08-18 v1: switched back to TSSOP-16 package shift register for better switching characteristics; routed entire pcb
2022-08-18 v1: gerbers generated and sent to JLCPCB for assembly
2022-08-19 v1: regenerate gerber and drill files with tooling holes per request by JLCPCB
2022-08-20 v1: regenerate gerbers with footprint values rendered on silkscreen; these will be missing on initial JLCPCB order
2022-08-29 fw: a decent first pass at attempting to communicate with PSRAM via PIO SPI
2022-08-29 fw: working SPI read EID command; C control over CE# pin is necessary; PIO controls CLK and IO instead
2022-08-29 fw: mark psram functions time critical to get logic analyzer capture back; CE#=0 is too long and CE#=1 is too short
2022-08-29 fw: set clock to 266MHz and PSRAM falls apart
2022-08-30 fw: PIO code for partially successful SPI; misaligned reads
2022-08-30 fw: adjusted PIO code for 133MHz
2022-08-31 fw: working PIO for SPI with write and read commands
2022-08-31 fw: double clock speed and double PIO sample loops
2022-08-31 fw: added working QSPI mode with successful quad-read test
2022-08-31 fw: enable DMA transfers from RX FIFO for SPI/QSPI
2022-09-01 fw: implemented general psram write/read methods
2022-09-02 fw: working QPI psram read function with PIO
2022-09-02 fw: now working at 266MHz
2022-09-03 fw: generate slow 3.58MHz pulse on SNES CE# line for testing
2022-09-04 fw: doing simple logic_analyzer read testing to see whats on the pins for the other devices; running into pico stdio_usb issues
2022-09-05 fw: TODO note about plan with PIO and DMA channels
2022-09-05 fw: move prototype code to proto/
2022-09-05 fw: reset to basic PIO program to PSRAM SPI to emit arbitrary bytes on the wire with auto-control of PSRAM_CE# line
2022-09-06 fw: fixed to not skip second command
2022-09-06 fw: implement QPI mode switch and QPI write/read PIOs
2022-09-06 fw: using side_set opt(ional) to allow both write and read programs to run simultaneously in pull state
2022-09-06 fw: separate address from data in fifo elements; working on timing for qpi read
2022-09-06 fw: fixed qpi read timing
